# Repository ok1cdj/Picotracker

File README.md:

Picotracker
===========

Very small tracker with GPS and 430MHz CW/RTTY radio beacon designed for High Altitude Baloons.
Based on ATMega328 @4MHz and powered from single AA Lithium 1.5 V cell

Radio is RFM22 for 430 MHz. PCB is designed for both versions.

GPS is uBLOX MAX-6G or MAX-M8C Module from [HAB supplies] (http://ava.upuaut.net/store/index.php?route=product/product&path=59_64&product_id=71)
Tracker send CW an RTTY messages. 
You can find source code under sw directory.

We can offer bare PCB or KIT without GPS and antenna. 
http://hamshop.cz/hab-a-aprs-c34/

**Be careful, voltage over 1.8 V can damage MAX-6G GPS module. Install power supply first, and measure voltage at output.**

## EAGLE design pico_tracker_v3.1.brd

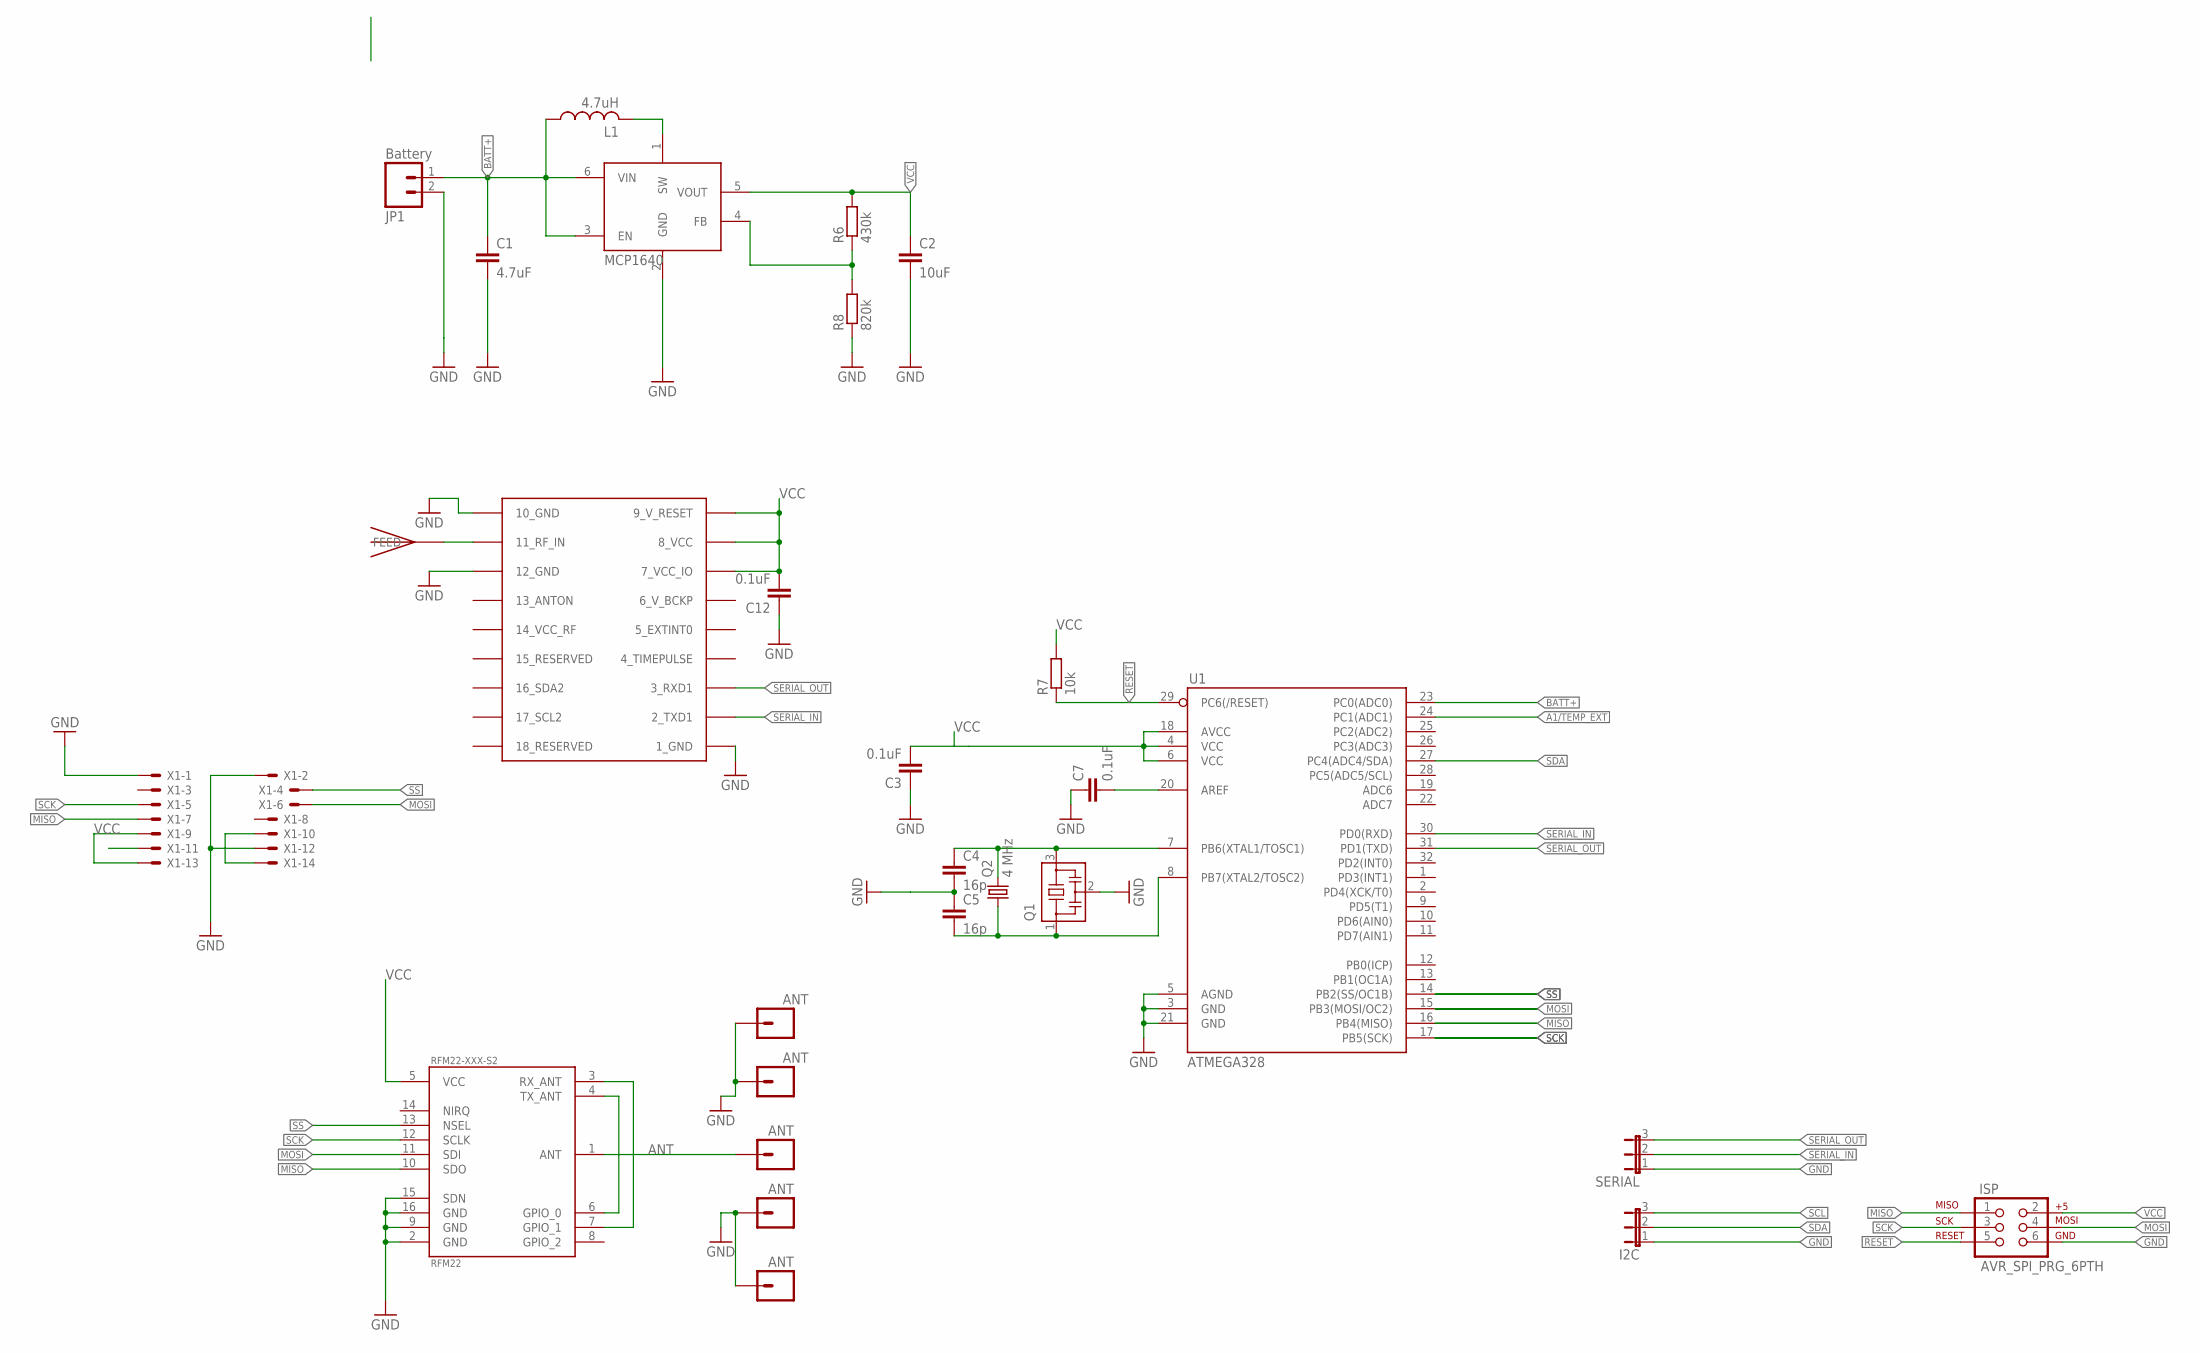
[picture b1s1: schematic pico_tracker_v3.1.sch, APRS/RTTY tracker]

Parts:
C1: 4.7uF; C0805
C2: 10uF; C0805
C3, C7, C12: 0.1uF; C0603
C4, C5: 16p; C0603
GND, GND17: ANT; 1X01
GPS_ANT: JTI_ANTENNA-1575AT43A40
I2C: JP2E; JP2
ISP: AVR_SPI_PRG_6PTH; 2X3
JP1: Battery; 1X02
JP2, JP3, JP4: ANT; 1X01
L1: 4.7uH; LQH44
Q1: CSTCR6M00G53Z; CSTCR6M
Q2: 4 MHz; ABM03_HC49
R6: 430k; R0603
R7: 10k; R0603
R8: 820k; R0603
RFM22-XXX-S2: RFM22; RFM22-XXX-S2
SERIAL: JP2E; JP2
U1: ATMEGA328; TQFP32-08
U2: MCP1640; SOT23-6
U$3: UBLOX_MAX-6
X1: 87758-1416

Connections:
A1/TEMP_EXT: U1.24 (PC1(ADC1))
ANT: JP2.1, RFM22-XXX-S2.1 (ANT)
AREF: C7.2, U1.20 (AREF)
BATT+: C1.1, JP1.1, L1.P$1 (1), U1.23 (PC0(ADC0)), U2.3 (EN), U2.6 (VIN)
GND: C1.2, C2.2, C3.1, C4.2, C5.1, C7.1, C12.1, GND.1, GND17.1, I2C.1, ISP.6, JP1.2, JP3.1, JP4.1, Q1.2, R8.1, RFM22-XXX-S2.2 (GND), RFM22-XXX-S2.9 (GND), RFM22-XXX-S2.15 (SDN), RFM22-XXX-S2.16 (GND), SERIAL.1, U1.3 (GND), U1.5 (AGND), U1.21 (GND), U2.2 (GND), U$3.1_GND, U$3.10_GND, U$3.12_GND, X1.1, X1.2, X1.12
GPS_ANT: GPS_ANT.FEED, U$3.11_RF_IN
MISO: ISP.1, RFM22-XXX-S2.10 (SDO), U1.16 (PB4(MISO)), X1.7
MOSI: ISP.4, RFM22-XXX-S2.11 (SDI), U1.15 (PB3(MOSI/OC2)), X1.6
unnamed: X1.9, X1.13
unnamed: X1.10, X1.14
unnamed: RFM22-XXX-S2.4 (TX_ANT), RFM22-XXX-S2.6 (GPIO_0)
unnamed: RFM22-XXX-S2.3 (RX_ANT), RFM22-XXX-S2.7 (GPIO_1)
unnamed: L1.P$2 (2), U2.1 (SW)
unnamed: C4.1, Q1.3, Q2.2, U1.7 (PB6(XTAL1/TOSC1))
unnamed: C5.2, Q1.1, Q2.1, U1.8 (PB7(XTAL2/TOSC2))
unnamed: R6.1, R8.2, U2.4 (FB)
RESET: ISP.5, R7.1, U1.29 (PC6(/RESET))
SCK: ISP.3, RFM22-XXX-S2.12 (SCLK), U1.17 (PB5(SCK)), X1.5
SCL: I2C.3
SDA: I2C.2, U1.27 (PC4(ADC4/SDA))
SERIAL_IN: SERIAL.2, U1.30 (PD0(RXD)), U$3.2_TXD1
SERIAL_OUT: SERIAL.3, U1.31 (PD1(TXD)), U$3.3_RXD1
SS: RFM22-XXX-S2.13 (NSEL), U1.14 (PB2(SS/OC1B)), X1.4
VCC: C2.1, C3.2, C12.2, ISP.2, R6.2, R7.2, RFM22-XXX-S2.5 (VCC), U1.4 (VCC), U1.6 (VCC), U1.18 (AVCC), U2.5 (VOUT), U$3.7_VCC_IO, U$3.8_VCC, U$3.9_V_RESET, X1.11

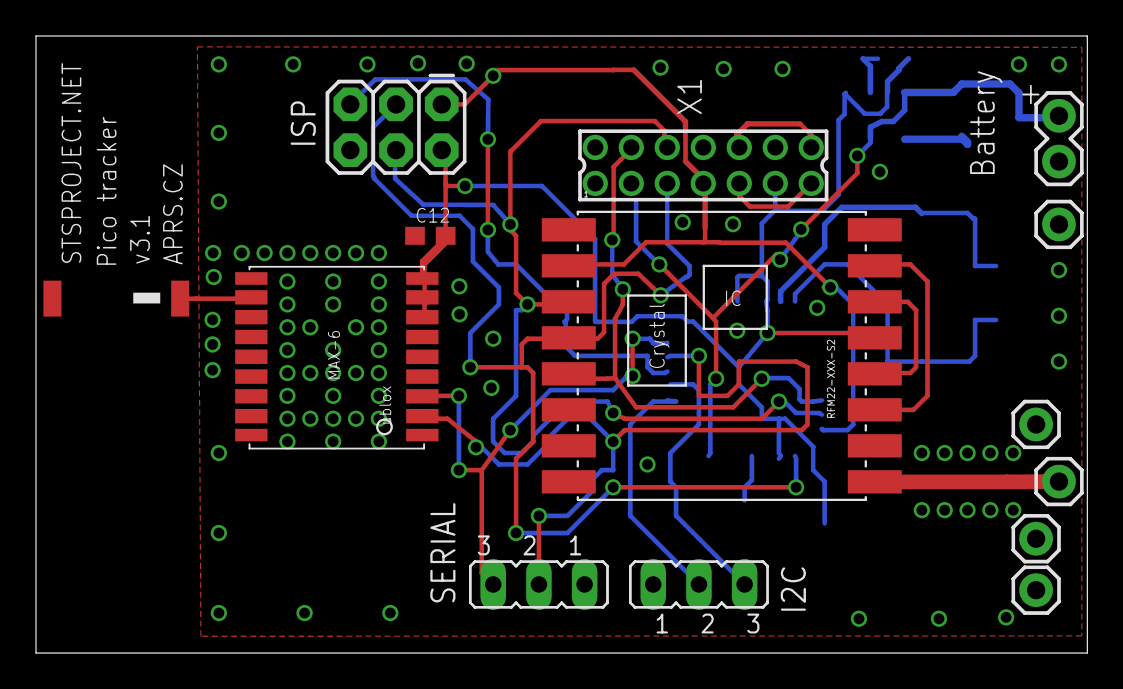
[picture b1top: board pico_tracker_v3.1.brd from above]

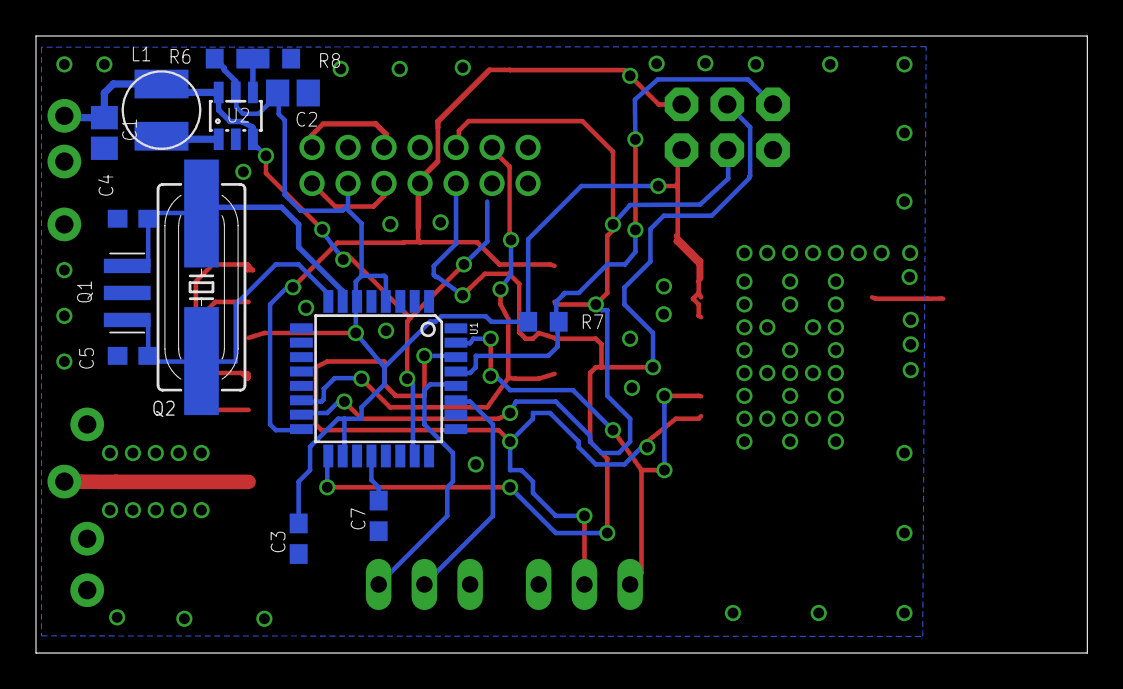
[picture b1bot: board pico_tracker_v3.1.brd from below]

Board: 2 copper layers, 58.4 x 34.3 mm, 28 parts (14 on the bottom side), 22 nets.

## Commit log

2014-05-17 added some files
2014-05-21 added picture of tracker
2014-05-21 new readme
2014-05-21 mod readme
2014-05-28 Warning about voltage in README.
2014-05-28 Minor change..
2014-11-03 New version of PCB and power safe mode for GPS
